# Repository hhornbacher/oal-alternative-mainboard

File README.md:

# Alternative mainboard for OpenAutoLab

The [OpenAutoLab](https://github.com/kauzerei/openautolab) is a automatic film processor developed by [@kauzerei](https://github.com/kauzerei).

I've designed an alternative mainboard based on an ESP32-S3 to also support transfer of development processes via BLE (and in future maybe WiFI with web interface).

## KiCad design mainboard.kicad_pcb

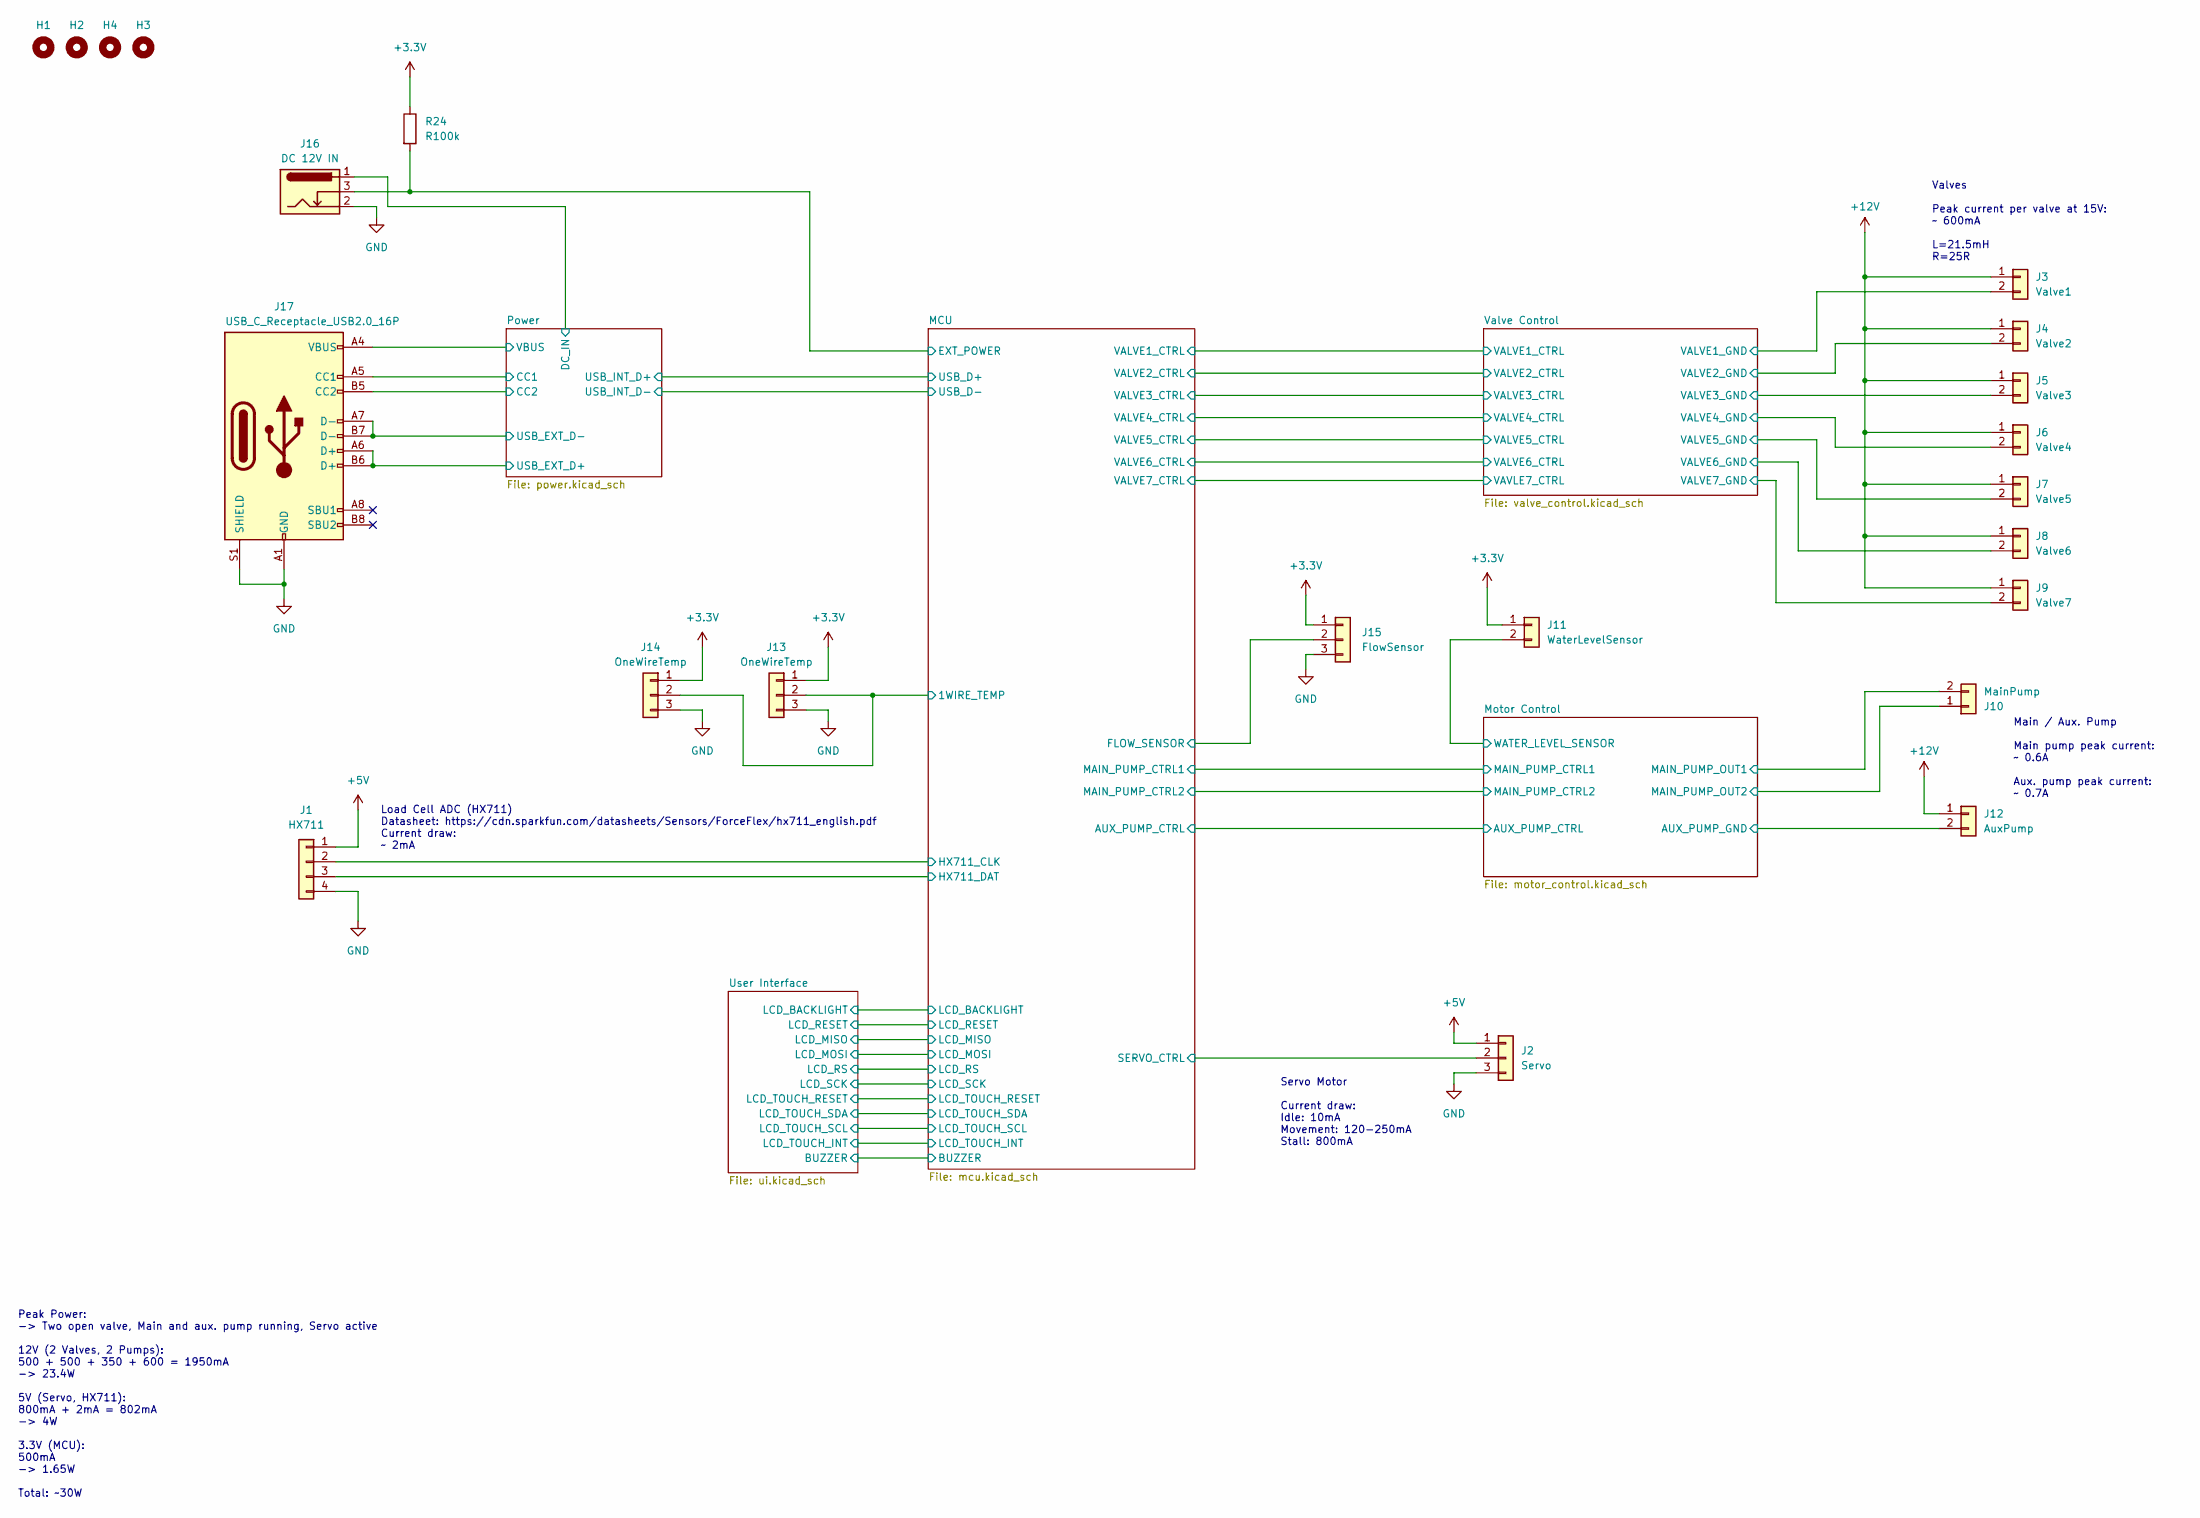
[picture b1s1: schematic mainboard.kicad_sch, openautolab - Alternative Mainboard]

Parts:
H1, H2, H3, H4: MountingHole; MountingHole_2.2mm_M2
J1: HX711; JST_XH_B4B-XH-A_1x04_P2.50mm_Vertical
J2: Servo; JST_XH_B3B-XH-A_1x03_P2.50mm_Vertical
J3: Valve1; JST_XH_B2B-XH-A_1x02_P2.50mm_Vertical
J4: Valve2; JST_XH_B2B-XH-A_1x02_P2.50mm_Vertical
J5: Valve3; JST_XH_B2B-XH-A_1x02_P2.50mm_Vertical
J6: Valve4; JST_XH_B2B-XH-A_1x02_P2.50mm_Vertical
J7: Valve5; JST_XH_B2B-XH-A_1x02_P2.50mm_Vertical
J8: Valve6; JST_XH_B2B-XH-A_1x02_P2.50mm_Vertical
J9: Valve7; JST_XH_B2B-XH-A_1x02_P2.50mm_Vertical
J10: MainPump; JST_XH_B2B-XH-A_1x02_P2.50mm_Vertical
J11: WaterLevelSensor; JST_XH_B2B-XH-A_1x02_P2.50mm_Vertical
J12: AuxPump; JST_XH_B2B-XH-A_1x02_P2.50mm_Vertical
J13, J14: OneWireTemp; JST_XH_B3B-XH-A_1x03_P2.50mm_Vertical
J15: FlowSensor; JST_XH_B3B-XH-A_1x03_P2.50mm_Vertical
J16: DC 12V IN; BarrelJack_Wuerth_6941xx301002; Mouser Part Number 710-694106301002
J17: USB_C_Receptacle_USB2.0_16P; USB_C_Receptacle_JAE_DX07S016JA1R1500; Mouser Part Number 656-DX07S016JA1R1500
R24: R100k; R_0805_2012Metric; Mouser Part Number 660-RK73B2ATTD104J

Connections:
+3.3V: J11.1, J13.1, J14.1, J15.1, R24.1; also elsewhere on the board
+5V: J1.1, J2.1; also elsewhere on the board
+12V: J3.1, J4.1, J5.1, J6.1, J7.1, J8.1, J9.1, J12.1; also elsewhere on the board
/MCU/1WIRE_TEMP: J13.2, J14.2; also elsewhere on the board
/MCU/EXT_POWER: J16.3, R24.2; also elsewhere on the board
/MCU/FLOW_SENSOR: J15.2; also elsewhere on the board
/MCU/HX711_CLK: J1.2; also elsewhere on the board
/MCU/HX711_DAT: J1.3; also elsewhere on the board
/MCU/SERVO_CTRL: J2.2; also elsewhere on the board
/Motor Control/AUX_PUMP_GND: J12.2; also elsewhere on the board
/Motor Control/MAIN_PUMP_OUT1: J10.2; also elsewhere on the board
/Motor Control/MAIN_PUMP_OUT2: J10.1; also elsewhere on the board
/Motor Control/WATER_LEVEL_SENSOR: J11.2; also elsewhere on the board
/Power/CC1: J17.A5 (CC1); also elsewhere on the board
/Power/CC2: J17.B5 (CC2); also elsewhere on the board
/Power/DC_IN: J16.1; also elsewhere on the board
/Power/USB_EXT_D+: J17.A6 (D+), J17.B6 (D+); also elsewhere on the board
/Power/USB_EXT_D-: J17.A7 (D-), J17.B7 (D-); also elsewhere on the board
/Power/VBUS: J17.A4 (VBUS), J17.A9 (VBUS), J17.B4 (VBUS), J17.B9 (VBUS); also elsewhere on the board
/Valve Control/VALVE1_GND: J3.2; also elsewhere on the board
/Valve Control/VALVE2_GND: J4.2; also elsewhere on the board
/Valve Control/VALVE3_GND: J5.2; also elsewhere on the board
/Valve Control/VALVE4_GND: J6.2; also elsewhere on the board
/Valve Control/VALVE5_GND: J7.2; also elsewhere on the board
/Valve Control/VALVE6_GND: J8.2; also elsewhere on the board
/Valve Control/VALVE7_GND: J9.2; also elsewhere on the board
GND: J1.4, J2.3, J13.3, J14.3, J15.3, J16.2, J17.A1 (GND), J17.A12 (GND), J17.B1 (GND), J17.B12 (GND), J17.S1 (SHIELD); also elsewhere on the board

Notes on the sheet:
Peak Power: -> Two open valve, Main and aux. pump running, Servo active 12V (2 Valves, 2 Pumps): 500 + 500 + 350 + 600 = 1950mA -> 23.4W 5V (Servo, HX711): 800mA + 2mA = 802mA -> 4W 3.3V (MCU): 500mA -> 1.65W Total: ~30W
Load Cell ADC (HX711) Datasheet: https://cdn.sparkfun.com/datasheets/Sensors/ForceFlex/hx711_english.pdf Current draw: ~ 2mA
Valves Peak current per valve at 15V: ~ 600mA L=21.5mH R=25R
Servo Motor Current draw: Idle: 10mA Movement: 120-250mA Stall: 800mA
Main / Aux. Pump Main pump peak current: ~ 0.6A Aux. pump peak current: ~ 0.7A

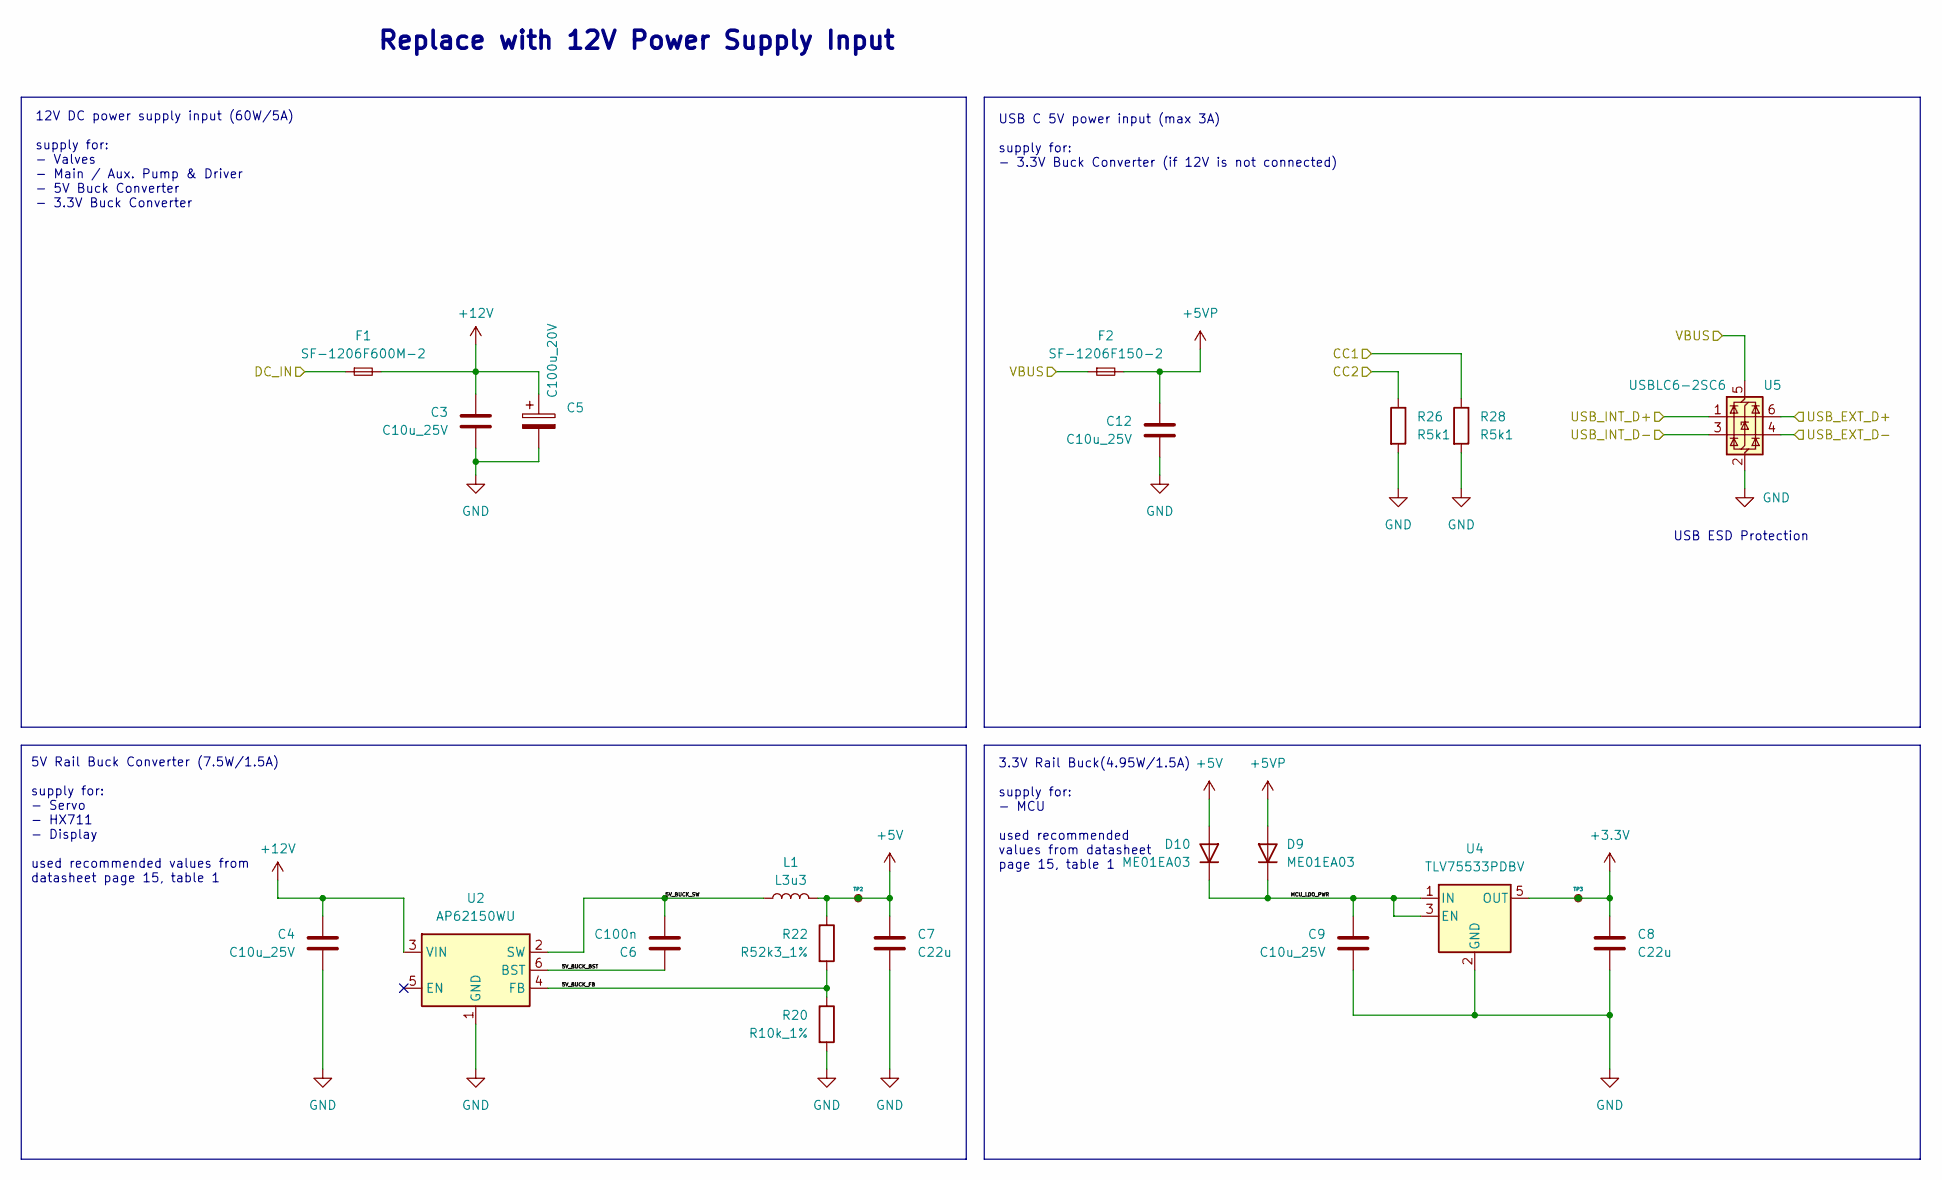
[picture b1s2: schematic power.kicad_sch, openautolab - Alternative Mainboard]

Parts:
C3, C4, C9, C12: C10u_25V; C_0603_1608Metric; Mouser Part Number 81-GRM188R61E106KA3J
C5: C100u_20V; CP_Elec_6.3x5.9; Mouser Part Number 647-PCM1D101MCL1GS
C6: C100n; C_0603_1608Metric; Mouser Part Number 80-C0603C104K3R7867
C7, C8: C22u; C_0805_2012Metric; Mouser Part Number 187-CL21A226MQQNNNF
D9, D10: ME01EA03; D_SOD-128; Mouser Part Number 581-ME01EA03
F1: SF-1206F600M-2; Fuse_1206_3216Metric; Mouser Part Number 652-SF-1206F600M-2
F2: SF-1206F150-2; Fuse_1206_3216Metric; Mouser Part Number 652-SF-1206F150-2
L1: L3u3; L_Coilcraft_LPS4018; Mouser Part Number 994-LPS4018-332MRC
R20: R10k_1%; R_0805_2012Metric; Mouser Part Number 71-CRCW0805-10K-E3
R22: R52k3_1%; R_0805_2012Metric; Mouser Part Number 652-CR0805FX-5232ELF
R26, R28: R5k1; R_0603_1608Metric; Mouser Part Number 667-ERJ-3EKF5101V
TP2, TP3: TestPoint_Small; TestPoint_Pad_D1.5mm
U2: AP62150WU; TSOT-23-6; Mouser Part Number 621-AP62150WU-7
U4: TLV75533PDBV; SOT-23-5; Mouser Part Number 595-TLV75533PDBVR
U5: USBLC6-2SC6; SOT-23-6; Mouser Part Number 511-USBLC6-2SC6

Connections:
+3.3V: C8.1, TP3.1, U4.5 (OUT); also elsewhere on the board
+5V: C7.1, D10.2 (A), L1.2, R22.1, TP2.1; also elsewhere on the board
+5VP: C12.1, D9.2 (A), F2.2
+12V: C3.1, C4.1, C5.1, F1.2, U2.3 (VIN); also elsewhere on the board
/MCU/USB_D+: U5.1 (I/O1); also elsewhere on the board
/MCU/USB_D-: U5.3 (I/O2); also elsewhere on the board
/Power/5V_BUCK_BST: C6.2, U2.6 (BST)
/Power/5V_BUCK_FB: R20.1, R22.2, U2.4 (FB)
/Power/5V_BUCK_SW: C6.1, L1.1, U2.2 (SW)
/Power/CC1: R28.1; also elsewhere on the board
/Power/CC2: R26.1; also elsewhere on the board
/Power/DC_IN: F1.1; also elsewhere on the board
/Power/MCU_LDO_PWR: C9.1, D9.1 (K), D10.1 (K), U4.1 (IN), U4.3 (EN)
/Power/USB_EXT_D+: U5.6 (I/O1); also elsewhere on the board
/Power/USB_EXT_D-: U5.4 (I/O2); also elsewhere on the board
/Power/VBUS: F2.1, U5.5 (VBUS); also elsewhere on the board
GND: C3.2, C4.2, C5.2, C7.2, C8.2, C9.2, C12.2, R20.2, R26.2, R28.2, U2.1 (GND), U4.2 (GND), U5.2 (GND); also elsewhere on the board

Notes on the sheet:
5V Rail Buck Converter (7.5W/1.5A) supply for: - Servo - HX711 - Display used recommended values from datasheet page 15, table 1
USB C 5V power input (max 3A) supply for: - 3.3V Buck Converter (if 12V is not connected)
3.3V Rail Buck(4.95W/1.5A) supply for: - MCU used recommended values from datasheet page 15, table 1
USB ESD Protection
12V DC power supply input (60W/5A) supply for: - Valves - Main / Aux. Pump & Driver - 5V Buck Converter - 3.3V Buck Converter
Replace with 12V Power Supply Input

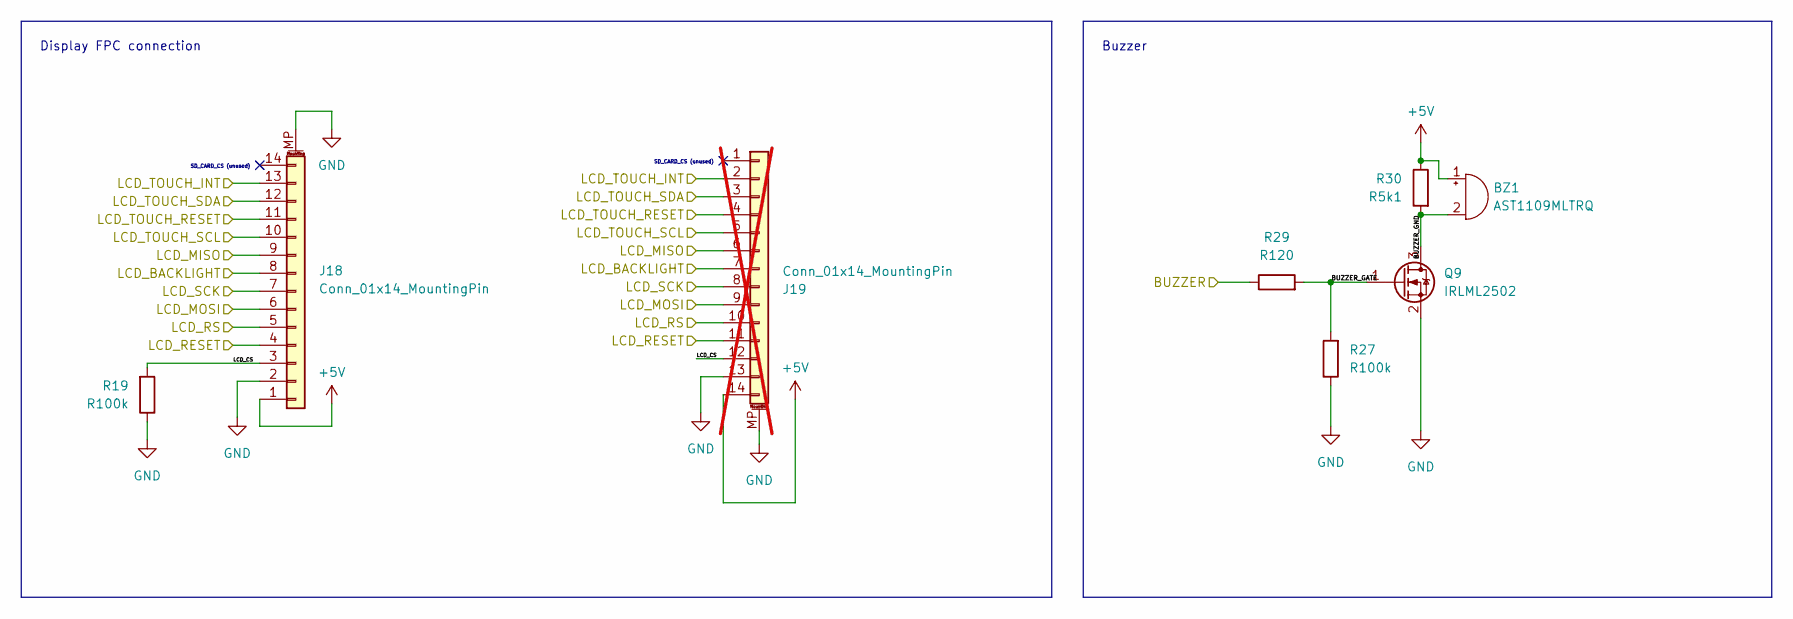
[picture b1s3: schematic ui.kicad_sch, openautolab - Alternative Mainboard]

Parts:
BZ1: AST1109MLTRQ; Buzzer_Mallory_AST1109MLTRQ; Mouser Part Number 539-AST1109MLTRQ
J18: Conn_01x14_MountingPin; XF2M-1415-1A; Mouser Part Number 653-XF2M-1415-1A
J19: Conn_01x14_MountingPin; XF2M-1415-1A; Mouser Part Number 653-XF2M-1415-1A; not fitted
Q9: IRLML2502; SOT-23; Mouser Part Number 942-IRLML2502TRPBF
R19, R27: R100k; R_0805_2012Metric; Mouser Part Number 660-RK73B2ATTD104J
R29: R120; R_0805_2012Metric; Mouser Part Number 603-AC0805FR-07120RL
R30: R5k1; R_0603_1608Metric; Mouser Part Number 667-ERJ-3EKF5101V

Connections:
+5V: BZ1.1 (+), J18.1, J19.14, R30.1; also elsewhere on the board
/MCU/BUZZER: R29.1; also elsewhere on the board
/MCU/LCD_BACKLIGHT: J18.8, J19.7; also elsewhere on the board
/MCU/LCD_MISO: J18.9, J19.6; also elsewhere on the board
/MCU/LCD_MOSI: J18.6, J19.9; also elsewhere on the board
/MCU/LCD_RESET: J18.4, J19.11; also elsewhere on the board
/MCU/LCD_RS: J18.5, J19.10; also elsewhere on the board
/MCU/LCD_SCK: J18.7, J19.8; also elsewhere on the board
/MCU/LCD_TOUCH_INT: J18.13, J19.2; also elsewhere on the board
/MCU/LCD_TOUCH_RESET: J18.11, J19.4; also elsewhere on the board
/MCU/LCD_TOUCH_SCL: J18.10, J19.5; also elsewhere on the board
/MCU/LCD_TOUCH_SDA: J18.12, J19.3; also elsewhere on the board
/User Interface/BUZZER_GATE: Q9.1 (G), R27.2, R29.2
/User Interface/BUZZER_GND: BZ1.2 (-), Q9.3 (D), R30.2
/User Interface/LCD_CS: J18.3, J19.12, R19.2
GND: J18.2, J18.MP (MountPin), J19.13, J19.MP (MountPin), Q9.2 (S), R19.1, R27.1; also elsewhere on the board

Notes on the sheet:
SD_CARD_CS (unused)
Display FPC connection
Buzzer

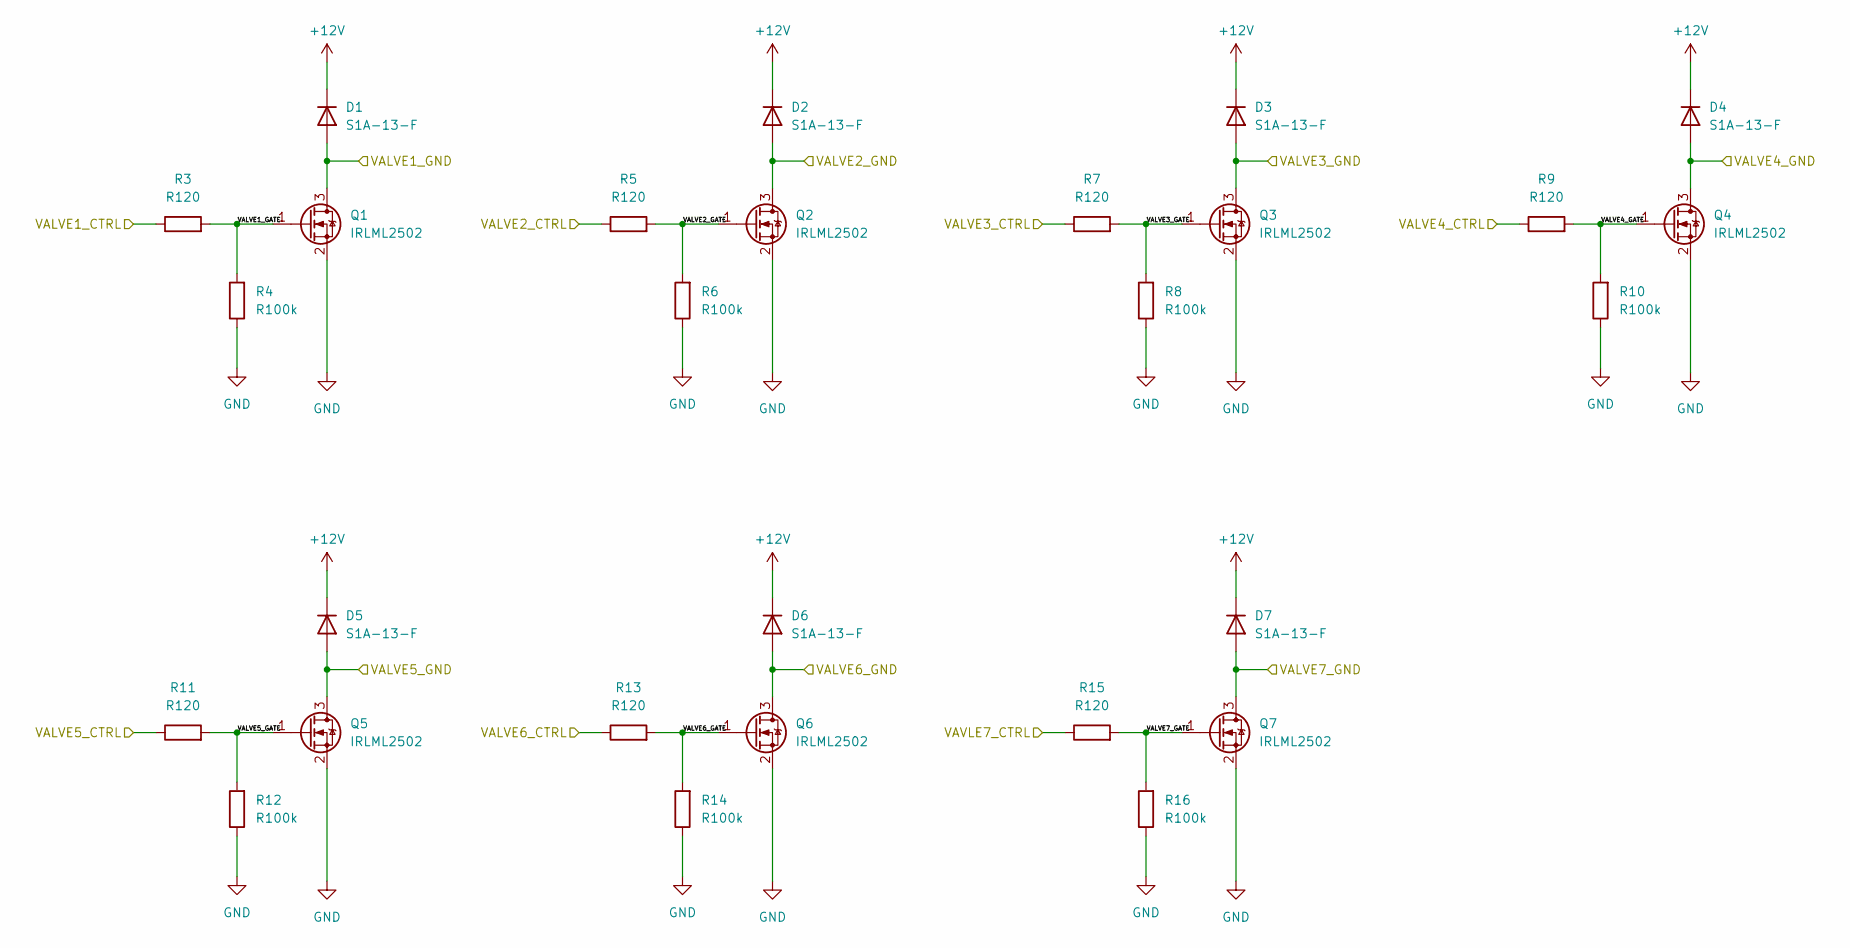
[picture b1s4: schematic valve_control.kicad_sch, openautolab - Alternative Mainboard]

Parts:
D1, D2, D3, D4, D5, D6, D7: S1A-13-F; D_SMA; Mouser Part Number 621-ES1A-F
Q1, Q2, Q3, Q4, Q5, Q6, Q7: IRLML2502; SOT-23; Mouser Part Number 942-IRLML2502TRPBF
R3, R5, R7, R9, R11, R13, R15: R120; R_0805_2012Metric; Mouser Part Number 603-AC0805FR-07120RL
R4, R6, R8, R10, R12, R14, R16: R100k; R_0805_2012Metric; Mouser Part Number 660-RK73B2ATTD104J

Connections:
+12V: D1.1 (K), D2.1 (K), D3.1 (K), D4.1 (K), D5.1 (K), D6.1 (K), D7.1 (K); also elsewhere on the board
/MCU/VALVE1_CTRL: R3.1; also elsewhere on the board
/MCU/VALVE2_CTRL: R5.1; also elsewhere on the board
/MCU/VALVE3_CTRL: R7.1; also elsewhere on the board
/MCU/VALVE4_CTRL: R9.1; also elsewhere on the board
/MCU/VALVE5_CTRL: R11.1; also elsewhere on the board
/MCU/VALVE6_CTRL: R13.1; also elsewhere on the board
/MCU/VALVE7_CTRL: R15.1; also elsewhere on the board
/Valve Control/VALVE1_GATE: Q1.1 (G), R3.2, R4.2
/Valve Control/VALVE1_GND: D1.2 (A), Q1.3 (D); also elsewhere on the board
/Valve Control/VALVE2_GATE: Q2.1 (G), R5.2, R6.2
/Valve Control/VALVE2_GND: D2.2 (A), Q2.3 (D); also elsewhere on the board
/Valve Control/VALVE3_GATE: Q3.1 (G), R7.2, R8.2
/Valve Control/VALVE3_GND: D3.2 (A), Q3.3 (D); also elsewhere on the board
/Valve Control/VALVE4_GATE: Q4.1 (G), R9.2, R10.2
/Valve Control/VALVE4_GND: D4.2 (A), Q4.3 (D); also elsewhere on the board
/Valve Control/VALVE5_GATE: Q5.1 (G), R11.2, R12.2
/Valve Control/VALVE5_GND: D5.2 (A), Q5.3 (D); also elsewhere on the board
/Valve Control/VALVE6_GATE: Q6.1 (G), R13.2, R14.2
/Valve Control/VALVE6_GND: D6.2 (A), Q6.3 (D); also elsewhere on the board
/Valve Control/VALVE7_GATE: Q7.1 (G), R15.2, R16.2
/Valve Control/VALVE7_GND: D7.2 (A), Q7.3 (D); also elsewhere on the board
GND: Q1.2 (S), Q2.2 (S), Q3.2 (S), Q4.2 (S), Q5.2 (S), Q6.2 (S), Q7.2 (S), R4.1, R6.1, R8.1, R10.1, R12.1, R14.1, R16.1; also elsewhere on the board

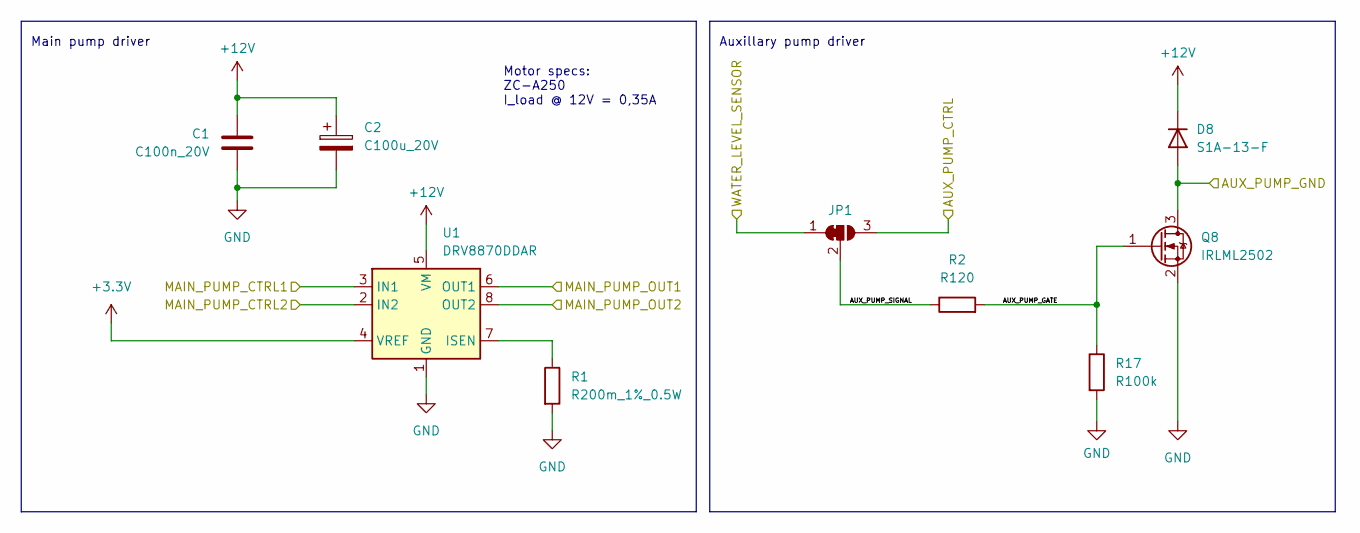
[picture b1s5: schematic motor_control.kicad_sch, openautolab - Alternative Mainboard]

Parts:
C1: C100n_20V; C_0805_2012Metric; Mouser Part Number 187-CL21B104KACNNNC
C2: C100u_20V; CP_Elec_6.3x5.9; Mouser Part Number 647-PCM1D101MCL1GS
D8: S1A-13-F; D_SMA; Mouser Part Number 621-ES1A-F
JP1: SolderJumper_3_Bridged12; SolderJumper-3_P1.3mm_Bridged12_RoundedPad1.0x1.5mm_NumberL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
Q8: IRLML2502; SOT-23; Mouser Part Number 942-IRLML2502TRPBF
R1: R200m_1%_0.5W; R_1206_3216Metric; Mouser Part Number 504-MFLA1206R2000FS
R2: R120; R_0805_2012Metric; Mouser Part Number 603-AC0805FR-07120RL
R17: R100k; R_0805_2012Metric; Mouser Part Number 660-RK73B2ATTD104J
U1: DRV8870DDAR; Texas_HTSOP-8-1EP_3.9x4.9mm_P1.27mm_EP2.95x4.9mm_Mask2.4x3.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; Mouser Part Number 595-DRV8870DDAR

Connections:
+3.3V: U1.4 (VREF); also elsewhere on the board
+12V: C1.1, C2.1, D8.1 (K), U1.5 (VM); also elsewhere on the board
/MCU/AUX_PUMP_CTRL: JP1.3 (B); also elsewhere on the board
/MCU/MAIN_PUMP_CTRL1: U1.3 (IN1); also elsewhere on the board
/MCU/MAIN_PUMP_CTRL2: U1.2 (IN2); also elsewhere on the board
/Motor Control/AUX_PUMP_GATE: Q8.1 (G), R2.2, R17.1
/Motor Control/AUX_PUMP_GND: D8.2 (A), Q8.3 (D); also elsewhere on the board
/Motor Control/AUX_PUMP_SIGNAL: JP1.2 (C), R2.1
/Motor Control/MAIN_PUMP_OUT1: U1.6 (OUT1); also elsewhere on the board
/Motor Control/MAIN_PUMP_OUT2: U1.8 (OUT2); also elsewhere on the board
/Motor Control/WATER_LEVEL_SENSOR: JP1.1 (A); also elsewhere on the board
GND: C1.2, C2.2, Q8.2 (S), R1.2, R17.2, U1.1 (GND), U1.9 (GND); also elsewhere on the board
unnamed: R1.1, U1.7 (ISEN)

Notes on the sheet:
Main pump driver
Motor specs: ZC-A250 I_load @ 12V = 0,35A
Auxillary pump driver

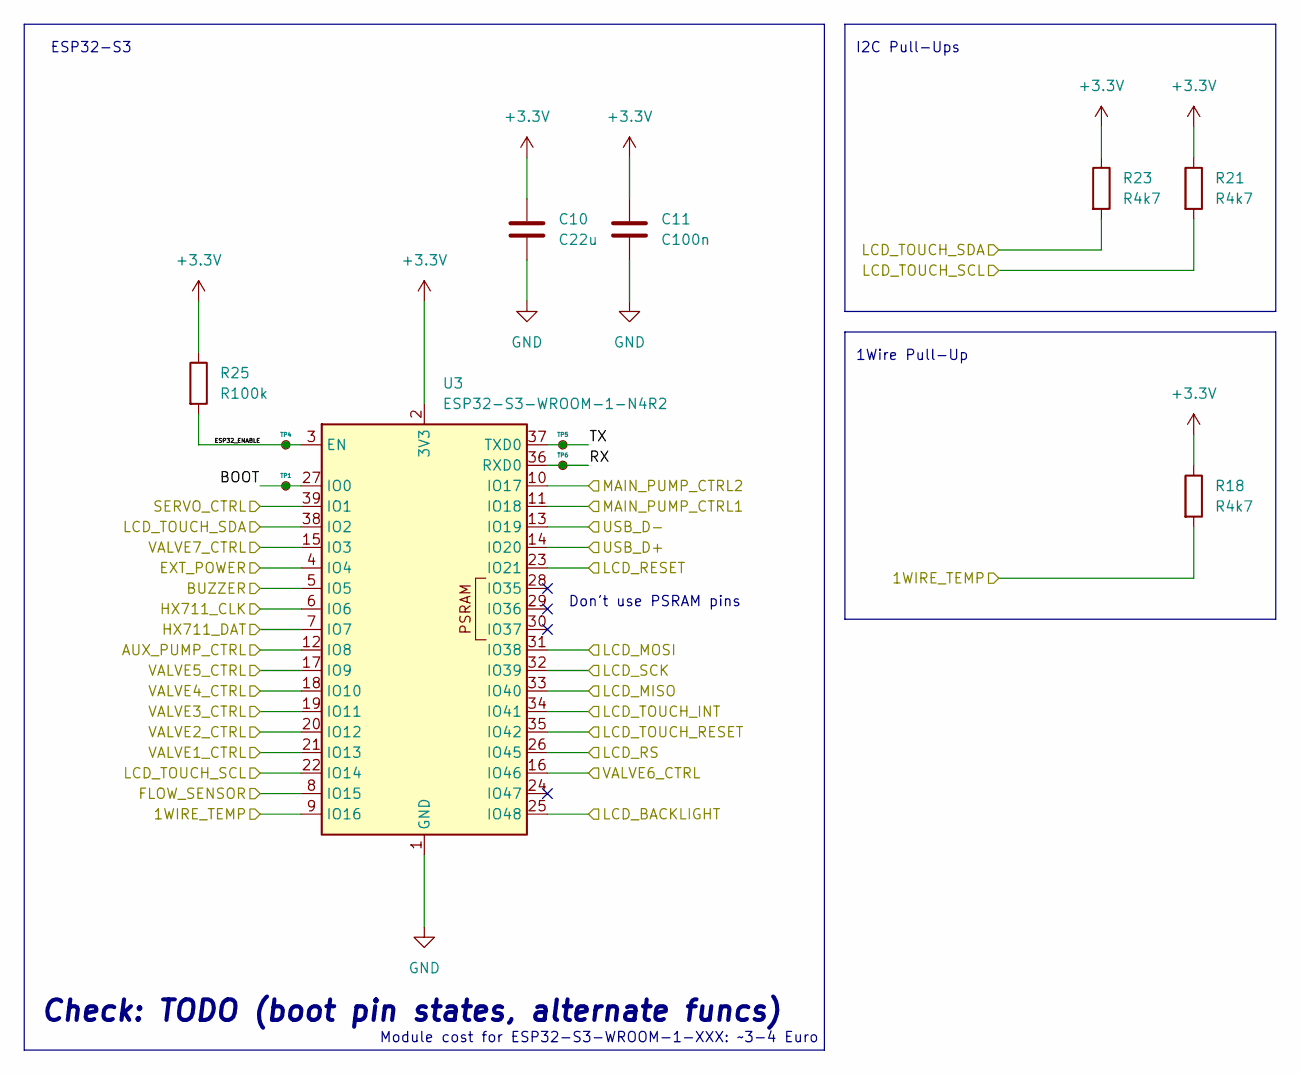
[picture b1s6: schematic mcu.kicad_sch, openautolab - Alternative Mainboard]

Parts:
C10: C22u; C_0805_2012Metric; Mouser Part Number 187-CL21A226MQQNNNF
C11: C100n; C_0603_1608Metric; Mouser Part Number 80-C0603C104K3R7867
R18, R21, R23: R4k7; R_0805_2012Metric; Mouser Part Number 279-CRGH0805F4K7
R25: R100k; R_0805_2012Metric; Mouser Part Number 660-RK73B2ATTD104J
TP1, TP4, TP5, TP6: TestPoint_Small; TestPoint_Pad_D1.5mm
U3: ESP32-S3-WROOM-1-N4R2; ESP32-S3-WROOM-1; Mouser Part Number 356-ESP32S3WROM1N4R2

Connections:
+3.3V: C10.1, C11.1, R18.1, R21.1, R23.1, R25.1, U3.2 (3V3); also elsewhere on the board
/MCU/1WIRE_TEMP: R18.2, U3.9 (IO16); also elsewhere on the board
/MCU/AUX_PUMP_CTRL: U3.12 (IO8); also elsewhere on the board
/MCU/BOOT: TP1.1, U3.27 (IO0)
/MCU/BUZZER: U3.5 (IO5); also elsewhere on the board
/MCU/ESP32_ENABLE: R25.2, TP4.1, U3.3 (EN)
/MCU/EXT_POWER: U3.4 (IO4); also elsewhere on the board
/MCU/FLOW_SENSOR: U3.8 (IO15); also elsewhere on the board
/MCU/HX711_CLK: U3.6 (IO6); also elsewhere on the board
/MCU/HX711_DAT: U3.7 (IO7); also elsewhere on the board
/MCU/LCD_BACKLIGHT: U3.25 (IO48); also elsewhere on the board
/MCU/LCD_MISO: U3.33 (IO40); also elsewhere on the board
/MCU/LCD_MOSI: U3.31 (IO38); also elsewhere on the board
/MCU/LCD_RESET: U3.23 (IO21); also elsewhere on the board
/MCU/LCD_RS: U3.26 (IO45); also elsewhere on the board
/MCU/LCD_SCK: U3.32 (IO39); also elsewhere on the board
/MCU/LCD_TOUCH_INT: U3.34 (IO41); also elsewhere on the board
/MCU/LCD_TOUCH_RESET: U3.35 (IO42); also elsewhere on the board
/MCU/LCD_TOUCH_SCL: R21.2, U3.22 (IO14); also elsewhere on the board
/MCU/LCD_TOUCH_SDA: R23.2, U3.38 (IO2); also elsewhere on the board
/MCU/MAIN_PUMP_CTRL1: U3.11 (IO18); also elsewhere on the board
/MCU/MAIN_PUMP_CTRL2: U3.10 (IO17); also elsewhere on the board
/MCU/RX: TP6.1, U3.36 (RXD0)
/MCU/SERVO_CTRL: U3.39 (IO1); also elsewhere on the board
/MCU/TX: TP5.1, U3.37 (TXD0)
/MCU/USB_D+: U3.14 (IO20); also elsewhere on the board
/MCU/USB_D-: U3.13 (IO19); also elsewhere on the board
/MCU/VALVE1_CTRL: U3.21 (IO13); also elsewhere on the board
/MCU/VALVE2_CTRL: U3.20 (IO12); also elsewhere on the board
/MCU/VALVE3_CTRL: U3.19 (IO11); also elsewhere on the board
/MCU/VALVE4_CTRL: U3.18 (IO10); also elsewhere on the board
/MCU/VALVE5_CTRL: U3.17 (IO9); also elsewhere on the board
/MCU/VALVE6_CTRL: U3.16 (IO46); also elsewhere on the board
/MCU/VALVE7_CTRL: U3.15 (IO3); also elsewhere on the board
GND: C10.2, C11.2, U3.1 (GND), U3.40 (GND), U3.41 (GND); also elsewhere on the board

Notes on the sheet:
Module cost for ESP32-S3-WROOM-1-XXX: ~3-4 Euro
ESP32-S3
Don't use PSRAM pins
Check: TODO (boot pin states, alternate funcs)
1Wire Pull-Up
I2C Pull-Ups

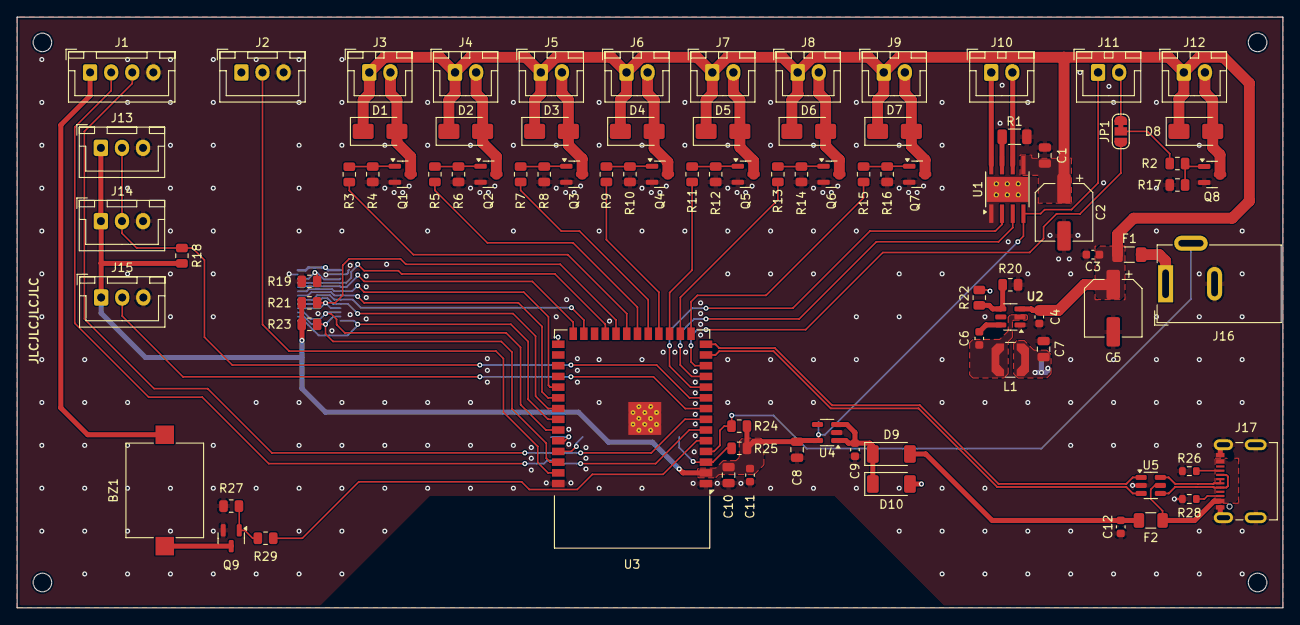
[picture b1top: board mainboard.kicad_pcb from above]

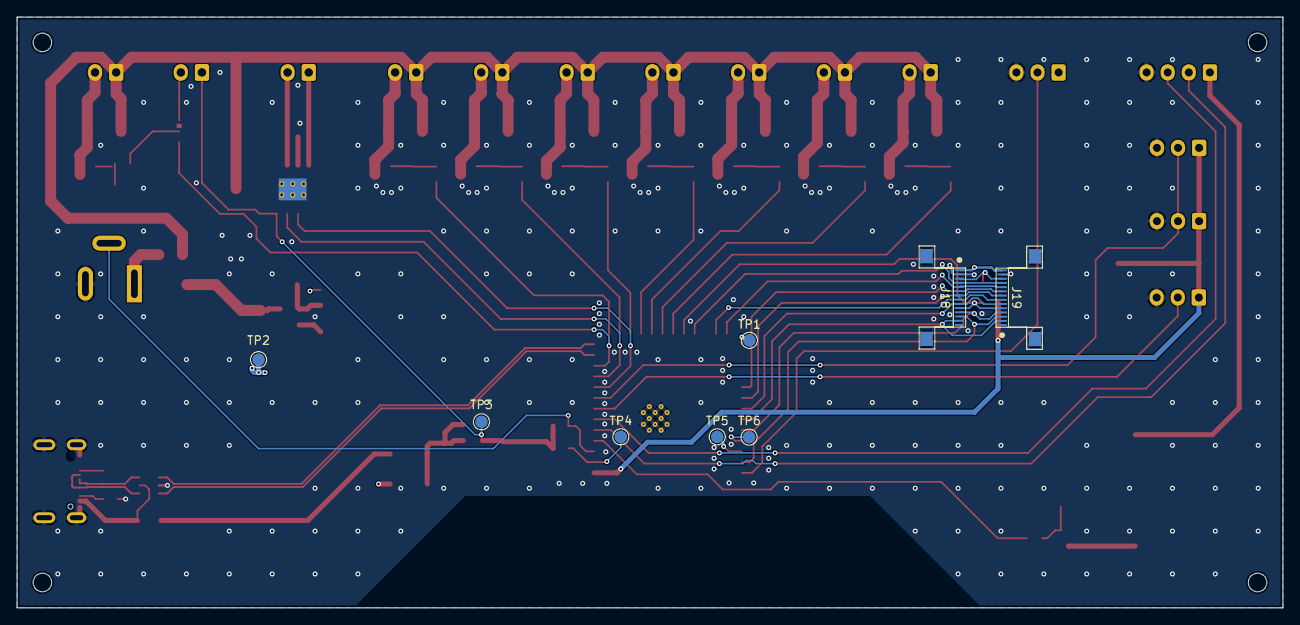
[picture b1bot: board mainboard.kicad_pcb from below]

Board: 4 copper layers, 150.0 x 70.0 mm, 99 parts (8 on the bottom side), 72 nets.

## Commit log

2024-04-03 Remove 12V buck converter and power rail
2024-04-03 Remove redundant hierarchical labels
2024-04-03 Add ESP32-S3-WROOM-1, 5V rail and UI sheet
2024-04-30 Finish first design
2024-05-02 Add reminder to replace fuse
2024-05-02 Add screen FPC to schematic and remove old OLED stuff
2024-05-02 Cleanup OLED stuff
2024-05-04 Fix LCD connector pin mapping and map them to MCU pins
2024-05-04 Cleanup
2024-05-05 Improve USB ESD connection
2024-05-05 Remove bottom pads from USB footprint
2024-05-05 Work on improving USB & power layout
2024-05-06 Finalize pin mapping, cleanup and layout
2024-05-06 Re-annotate parts by board
2024-05-12 Finish integration of TFT interface
2024-05-21 Redesign power rails to use barrel jack 12V input
2024-05-21 Cleanup layout and schematic
2024-05-21 Reannotate geographically by layout
2024-05-22 Final checks and cleanup
2024-05-23 Fix revision
2024-06-07 Add GND via stitching
2024-06-07 - Start Rev 2 - Add 5k1 resistor (R30) parallel to piezo (BZ1) - Remove redundant 5V wire from bottom at buck converter (U2)
2024-07-08 Fix revision on board
2024-07-08 Add readme and pictures
